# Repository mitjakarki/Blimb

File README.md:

# Blimb
Android app controllable robot arm, Bluetooth Limb.

A Fab Lab project made in Oulu.
Open source excluding the app, so feel free to customize the files. 

Contributors:
Mitja Kärki,
Janne Mustaniemi

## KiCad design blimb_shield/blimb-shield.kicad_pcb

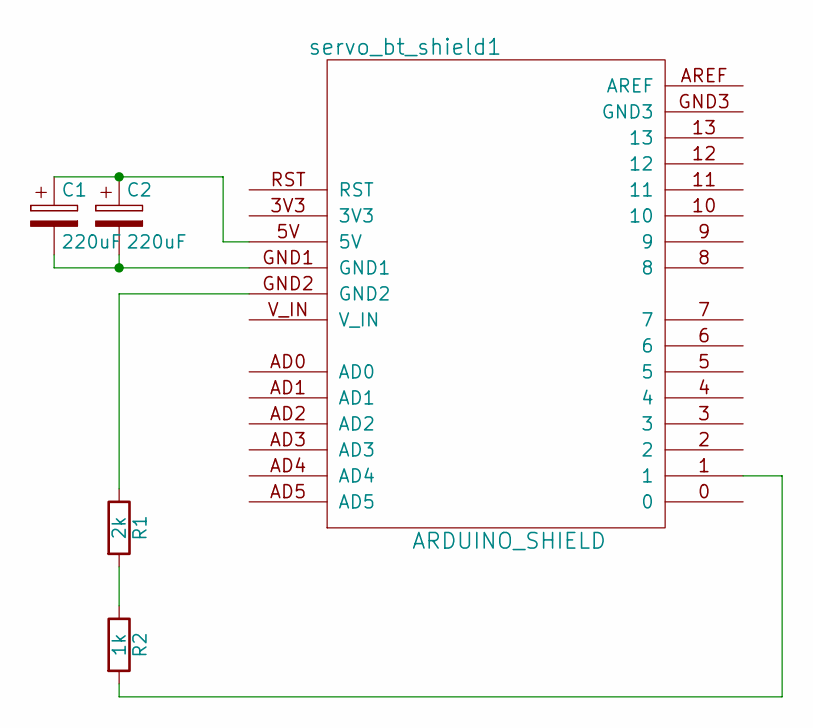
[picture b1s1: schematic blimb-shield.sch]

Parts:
C1, C2: 220uF; c_elec_10x10.5
R1: 2k; R_0805
R2: 1k; R_0805
servo_bt_shield1: ARDUINO_SHIELD; ARDUINO SHIELD

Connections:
unnamed: C1.1, C2.1, servo_bt_shield1.5V
unnamed: C1.2, C2.2, servo_bt_shield1.GND1
unnamed: R1.1, servo_bt_shield1.GND2
unnamed: R1.2, R2.1
unnamed: R2.2, servo_bt_shield1.1

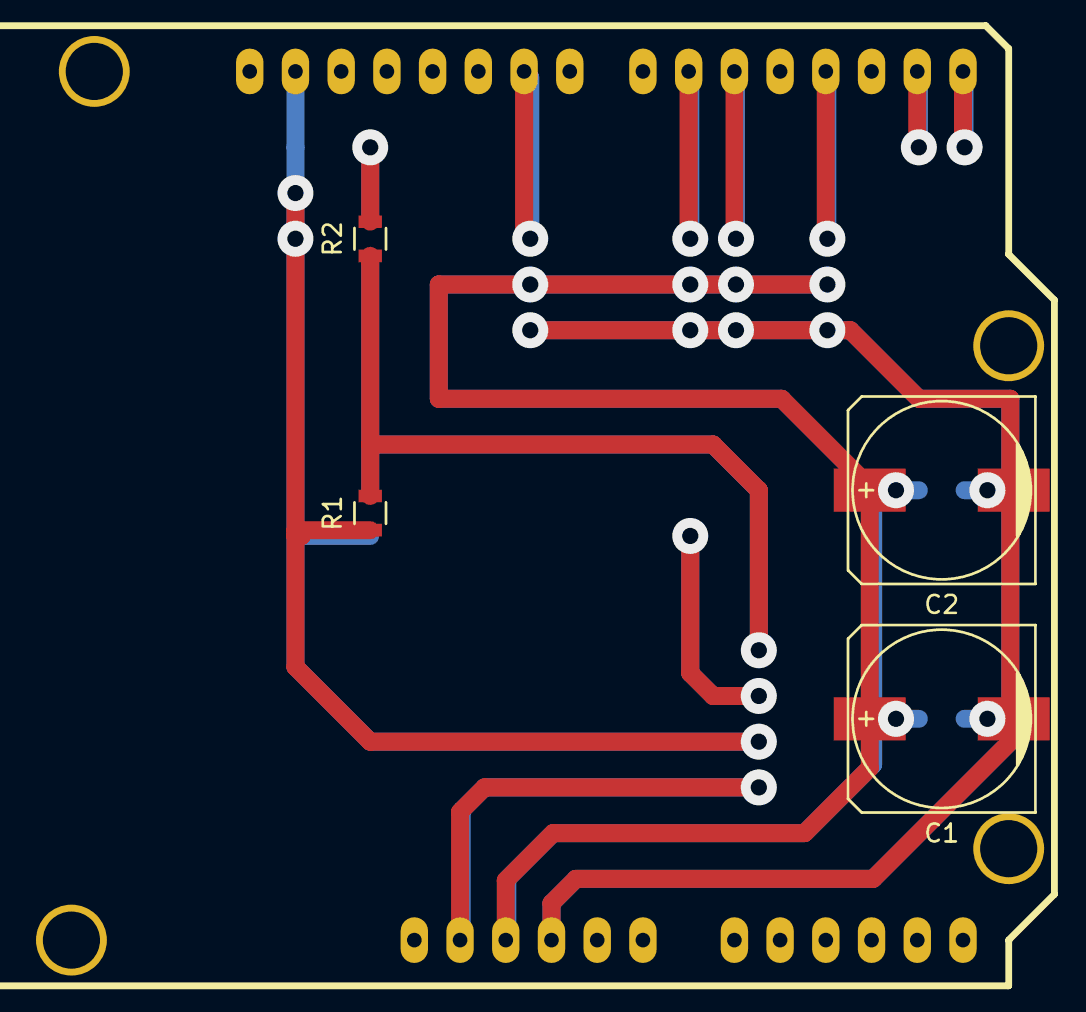
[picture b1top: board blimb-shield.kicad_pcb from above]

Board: 2 copper layers, 5 parts (0 on the bottom side), 5 nets.

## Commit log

2016-05-16 Added files to manufacture the whole robot
2016-05-21 Made a separate version for Arduino code with OLED debugging feature, removing it from the original.
2016-05-21 Added image folder
2016-05-21 Updated the creation manual
